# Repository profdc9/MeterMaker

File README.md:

# Meter Maker

A silly device for controlling analog galvanometers with a microcontroller.  It can take analog input or speaker voltage input
and output voltages for meters.

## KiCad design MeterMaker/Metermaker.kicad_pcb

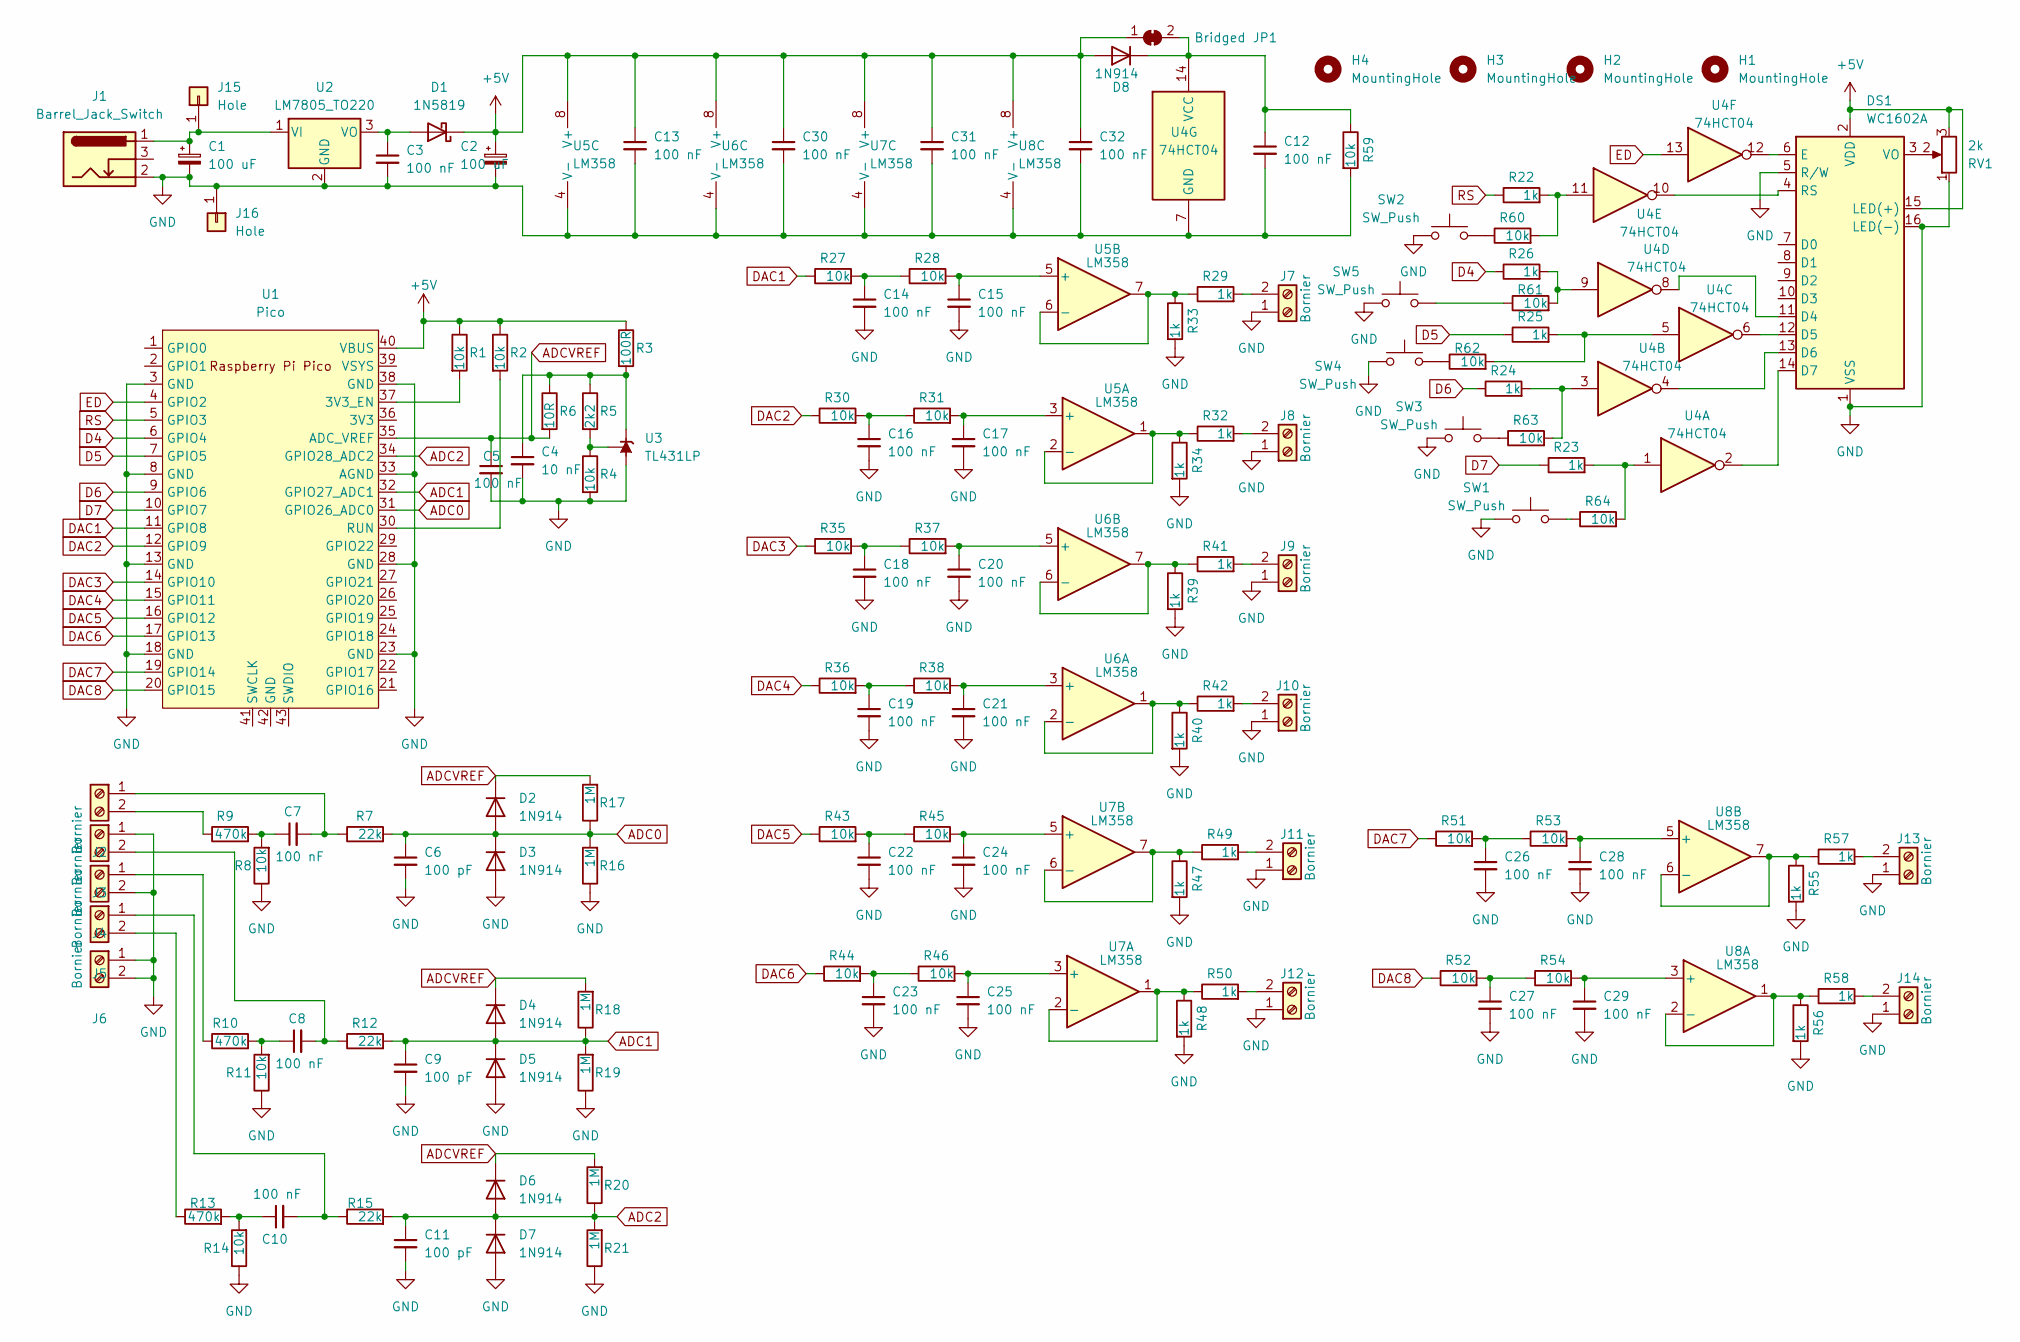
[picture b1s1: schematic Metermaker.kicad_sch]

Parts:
C1, C2: 100 uF; CP_Radial_D5.0mm_P2.50mm
C3, C5, C7, C8, C10, C12, C13, C14, C15, C16, C17, C18, C19, C20, C21, C22, C23, C24, C25, C26, C27, C28, C29, C30, C31, C32: 100 nF; C_Disc_D5.0mm_W2.5mm_P5.00mm
C4: 10 nF; C_Disc_D5.0mm_W2.5mm_P5.00mm
C6, C9, C11: 100 pF; C_Disc_D5.0mm_W2.5mm_P5.00mm
D1: 1N5819; D_DO-41_SOD81_P7.62mm_Horizontal
D2, D3, D4, D5, D6, D7, D8: 1N914; D_DO-35_SOD27_P7.62mm_Horizontal
DS1: WC1602A
H1, H2, H3, H4: MountingHole; MountingHole_3.2mm_M3
J1: Barrel_Jack_Switch; BarrelJack_Horizontal
J2, J3, J4, J5, J6, J7, J8, J9, J10, J11, J12, J13, J14: Bornier; TerminalBlock_bornier-2_P5.08mm
J15, J16: Hole; Pin_D1.3mm_L11.0mm
JP1: Bridged; SolderJumper-2_P1.3mm_Bridged2Bar_Pad1.0x1.5mm
R1, R2, R4, R8, R11, R14, R27, R28, R30, R31, R35, R36, R37, R38, R43, R44, R45, R46, R51, R52, R53, R54, R59, R60, R61, R62, R63, R64: 10k; R_Axial_DIN0207_L6.3mm_D2.5mm_P7.62mm_Horizontal
R3: 100R; R_Axial_DIN0207_L6.3mm_D2.5mm_P7.62mm_Horizontal
R5: 2k2; R_Axial_DIN0207_L6.3mm_D2.5mm_P7.62mm_Horizontal
R6: 10R; R_Axial_DIN0207_L6.3mm_D2.5mm_P7.62mm_Horizontal
R7, R12, R15: 22k; R_Axial_DIN0207_L6.3mm_D2.5mm_P7.62mm_Horizontal
R9, R10, R13: 470k; R_Axial_DIN0207_L6.3mm_D2.5mm_P7.62mm_Horizontal
R16, R17, R18, R19, R20, R21: 1M; R_Axial_DIN0207_L6.3mm_D2.5mm_P7.62mm_Horizontal
R22, R23, R24, R25, R26, R29, R32, R33, R34, R39, R40, R41, R42, R47, R48, R49, R50, R55, R56, R57, R58: 1k; R_Axial_DIN0207_L6.3mm_D2.5mm_P7.62mm_Horizontal
RV1: 2k; Potentiometer_Bourns_3296W_Vertical
SW1, SW2, SW3, SW4, SW5: SW_Push; SW_PUSH_6mm
U1: Pico; RPi_Pico_SMD_TH
U2: LM7805_TO220; TO-220-3_Vertical
U3: TL431LP; TO-92_Inline_Wide
U4: 74HCT04; DIP-14_W7.62mm_Socket
U5, U6, U7, U8: LM358; DIP-8_W7.62mm_Socket

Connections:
+5V: C2.1, C13.1, C30.1, C31.1, C32.1, D1.1 (K), D8.2 (A), DS1.2 (VDD), DS1.15 (LED(+)), JP1.1 (A), R1.1, R2.1, R3.1, RV1.3, U1.40 (VBUS), U5.8 (V+), U6.8 (V+), U7.8 (V+), U8.8 (V+)
ADC0: C6.1, D2.2 (A), D3.1 (K), R7.2, R16.2, R17.1, U1.31 (GPIO26_ADC0)
ADC1: C9.1, D4.2 (A), D5.1 (K), R12.2, R18.1, R19.2, U1.32 (GPIO27_ADC1)
ADC2: C11.1, D6.2 (A), D7.1 (K), R15.2, R20.1, R21.2, U1.34 (GPIO28_ADC2)
ADCVREF: C5.1, D2.1 (K), D4.1 (K), D6.1 (K), R6.2, R17.2, R18.2, R20.2, U1.35 (ADC_VREF)
D4: R26.1, U1.6 (GPIO4)
D5: R25.1, U1.7 (GPIO5)
D6: R24.1, U1.9 (GPIO6)
D7: R23.1, U1.10 (GPIO7)
DAC1: R27.1, U1.11 (GPIO8)
DAC2: R30.1, U1.12 (GPIO9)
DAC3: R35.1, U1.14 (GPIO10)
DAC4: R36.1, U1.15 (GPIO11)
DAC5: R43.1, U1.16 (GPIO12)
DAC6: R44.1, U1.17 (GPIO13)
DAC7: R51.1, U1.19 (GPIO14)
DAC8: R52.1, U1.20 (GPIO15)
ED: U1.4 (GPIO2), U4.13
GND: C1.2, C2.2, C3.2, C4.2, C5.2, C6.2, C9.2, C11.2, C12.2, C13.2, C14.2, C15.2, C16.2, C17.2, C18.2, C19.2, C20.2, C21.2, C22.2, C23.2, C24.2, C25.2, C26.2, C27.2, C28.2, C29.2, C30.2, C31.2, C32.2, D3.2 (A), D5.2 (A), D7.2 (A), DS1.1 (VSS), DS1.5 (R/W), DS1.16 (LED(-)), J1.2, J3.1, J4.2, J6.1, J6.2, J7.1, J8.1, J9.1, J10.1, J11.1, J12.1, J13.1, J14.1, J16.1, R4.2, R8.1, R11.1, R14.1, R16.1, R19.1, R21.1, R33.2, R34.2, R39.2, R40.2, R47.2, R48.2, R55.2, R56.2, R59.2, RV1.1, SW1.1, SW2.1, SW3.1, SW4.1, SW5.1, U1.3 (GND), U1.8 (GND), U1.13 (GND), U1.18 (GND), U1.23 (GND), U1.28 (GND), U1.33 (AGND), U1.38 (GND), U2.2 (GND), U3.2 (A), U4.7 (GND), U5.4 (V-), U6.4 (V-), U7.4 (V-), U8.4 (V-)
unnamed: C7.1, R8.2, R9.2
unnamed: C8.1, R10.2, R11.2
unnamed: C10.1, R13.2, R14.2
unnamed: C14.1, R27.2, R28.1
unnamed: C16.1, R30.2, R31.1
unnamed: C18.1, R35.2, R37.1
unnamed: C19.1, R36.2, R38.1
unnamed: C22.1, R43.2, R45.1
unnamed: C23.1, R44.2, R46.1
unnamed: C26.1, R51.2, R53.1
unnamed: C27.1, R52.2, R54.1
unnamed: C3.1, D1.2 (A), U2.3 (VO)
unnamed: C12.1, D8.1 (K), JP1.2 (B), R59.1, U4.14 (VCC)
unnamed: DS1.11 (D4), U4.8
unnamed: DS1.12 (D5), U4.6
unnamed: DS1.13 (D6), U4.4
unnamed: DS1.14 (D7), U4.2
unnamed: DS1.6 (E), U4.12
unnamed: DS1.4 (RS), U4.10
unnamed: DS1.3 (VO), RV1.2
unnamed: C7.2, J2.1, R7.1
unnamed: J2.2, R9.1
unnamed: C8.2, J3.2, R12.1
unnamed: J4.1, R10.1
unnamed: C10.2, J5.1, R15.1
unnamed: J5.2, R13.1
unnamed: J7.2, R29.2
unnamed: J8.2, R32.2
unnamed: J9.2, R41.2
unnamed: J10.2, R42.2
unnamed: J11.2, R49.2
unnamed: J12.2, R50.2
unnamed: J13.2, R57.2
unnamed: J14.2, R58.2
unnamed: C1.1, J1.1, J15.1, U2.1 (VI)
unnamed: R22.2, R60.2, U4.11
unnamed: R23.2, R64.2, U4.1
unnamed: R24.2, R63.2, U4.3
unnamed: R25.2, R62.2, U4.5
unnamed: R26.2, R61.2, U4.9
unnamed: R60.1, SW2.2
unnamed: R61.1, SW5.2
unnamed: R62.1, SW4.2
unnamed: R63.1, SW3.2
unnamed: R64.1, SW1.2
unnamed: R1.2, U1.37 (3V3_EN)
unnamed: R2.2, U1.30 (RUN)
unnamed: C4.1, R3.2, R5.1, R6.1, U3.3 (K)
unnamed: R4.1, R5.2, U3.1 (REF)
unnamed: C17.1, R31.2, U5.3 (+)
unnamed: R32.1, R34.1, U5.1, U5.2 (-)
unnamed: C15.1, R28.2, U5.5 (+)
unnamed: R29.1, R33.1, U5.6 (-), U5.7
unnamed: C21.1, R38.2, U6.3 (+)
unnamed: R40.1, R42.1, U6.1, U6.2 (-)
unnamed: C20.1, R37.2, U6.5 (+)
unnamed: R39.1, R41.1, U6.6 (-), U6.7
unnamed: C25.1, R46.2, U7.3 (+)
unnamed: R48.1, R50.1, U7.1, U7.2 (-)
unnamed: C24.1, R45.2, U7.5 (+)
unnamed: R47.1, R49.1, U7.6 (-), U7.7
unnamed: C29.1, R54.2, U8.3 (+)
unnamed: R56.1, R58.1, U8.1, U8.2 (-)
unnamed: C28.1, R53.2, U8.5 (+)
unnamed: R55.1, R57.1, U8.6 (-), U8.7
RS: R22.1, U1.5 (GPIO3)

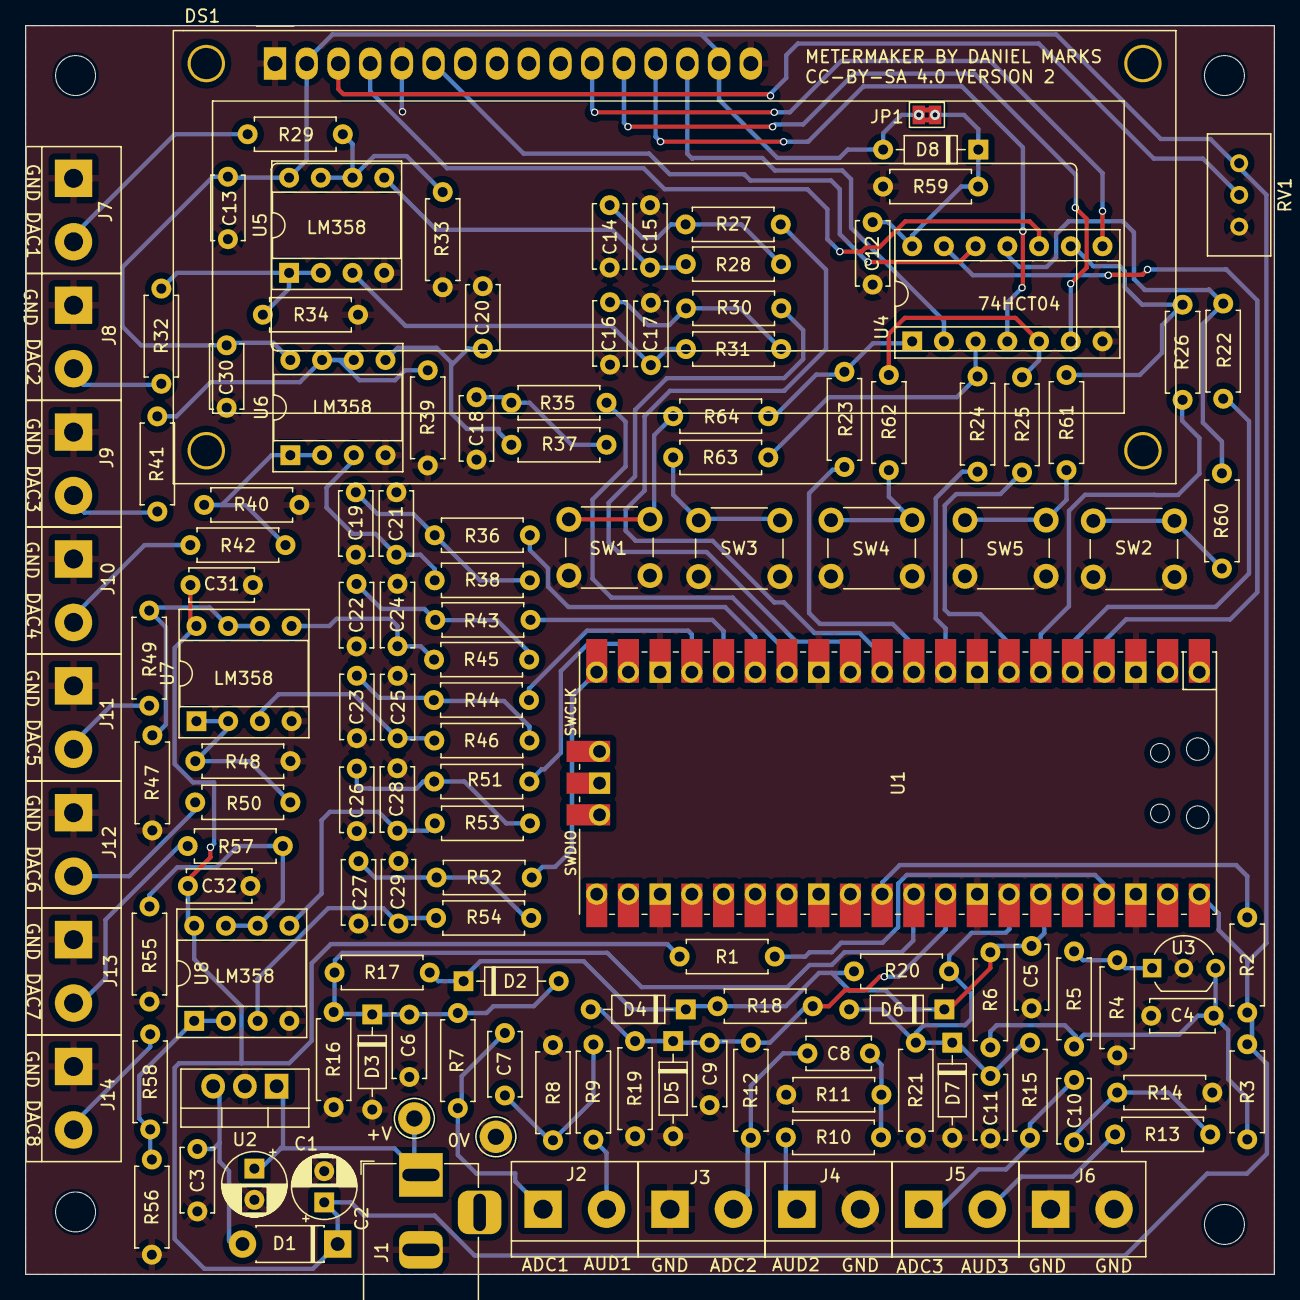
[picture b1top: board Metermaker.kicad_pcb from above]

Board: 2 copper layers, 100.0 x 100.0 mm, 140 parts (0 on the bottom side), 85 nets.

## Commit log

2025-01-04 First commit md
2025-01-18 Added initial code

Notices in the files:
MeterMaker/Metermaker.kicad_pcb:
CC-BY-SA 4.0 VERSION 2
